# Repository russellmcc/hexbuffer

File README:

This is a simple buffered multiple for eurorack modular synth systems.  Three buffered copies of each input are provided, and the second input is normalled to the first to provide six copies when there is only one input.

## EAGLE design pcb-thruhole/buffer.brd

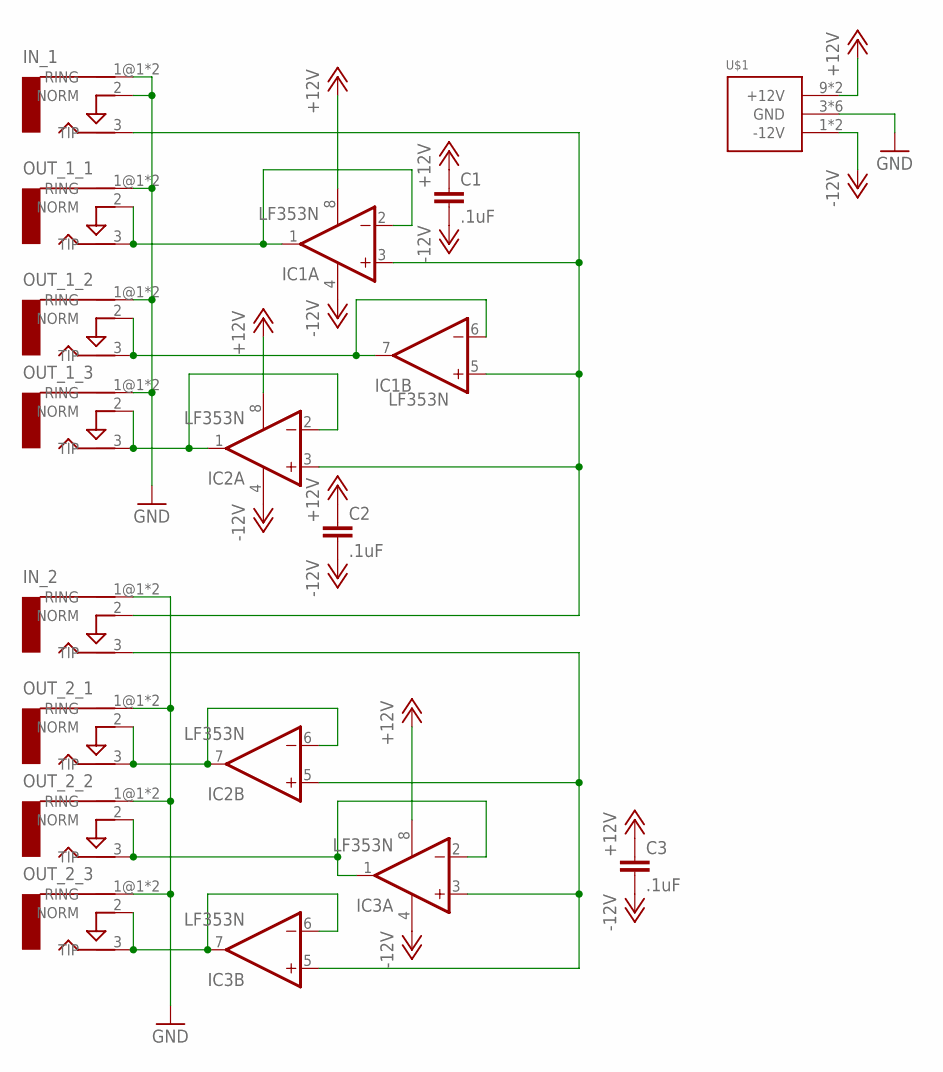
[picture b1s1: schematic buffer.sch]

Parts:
C1, C2, C3: .1uF; CAP-PTH-SMALL
IC1, IC2, IC3: LF353N; DIL08
IN_1, IN_2: AUDIO-JACKERTHENVAR; ERTHENVAR-JACK
OUT_1_1, OUT_1_2, OUT_1_3, OUT_2_1, OUT_2_2, OUT_2_3: AUDIO-JACKERTHENVAR; ERTHENVAR-JACK
U$1: POWER_SIMPLE16; POWER_16

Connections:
+12V: C1.1, C2.1, C3.1, IC1.8 (V+), IC2.8 (V+), IC3.8 (V+), U$1.9 (+12V), U$1.10 (+12V)
-12V: C1.2, C2.2, C3.2, IC1.4 (V-), IC2.4 (V-), IC3.4 (V-), U$1.1 (-12V), U$1.2 (-12V)
GND: IN_1.1@1 (RING), IN_1.1@2 (RING), IN_1.2 (NORM), IN_2.1@1 (RING), IN_2.1@2 (RING), OUT_1_1.1@1 (RING), OUT_1_1.1@2 (RING), OUT_1_2.1@1 (RING), OUT_1_2.1@2 (RING), OUT_1_3.1@1 (RING), OUT_1_3.1@2 (RING), OUT_2_1.1@1 (RING), OUT_2_1.1@2 (RING), OUT_2_2.1@1 (RING), OUT_2_2.1@2 (RING), OUT_2_3.1@1 (RING), OUT_2_3.1@2 (RING), U$1.3 (GND), U$1.4 (GND), U$1.5 (GND), U$1.6 (GND), U$1.7 (GND), U$1.8 (GND)
unnamed: IC1.1 (OUT), IC1.2 (-IN), OUT_1_1.2 (NORM), OUT_1_1.3 (TIP)
unnamed: IC2.1 (OUT), IC2.2 (-IN), OUT_1_3.2 (NORM), OUT_1_3.3 (TIP)
unnamed: IC1.6 (-IN), IC1.7 (OUT), OUT_1_2.2 (NORM), OUT_1_2.3 (TIP)
unnamed: IC1.3 (+IN), IC1.5 (+IN), IC2.3 (+IN), IN_1.3 (TIP), IN_2.2 (NORM)
unnamed: IC2.6 (-IN), IC2.7 (OUT), OUT_2_1.2 (NORM), OUT_2_1.3 (TIP)
unnamed: IC3.6 (-IN), IC3.7 (OUT), OUT_2_3.2 (NORM), OUT_2_3.3 (TIP)
unnamed: IC2.5 (+IN), IC3.3 (+IN), IC3.5 (+IN), IN_2.3 (TIP)
unnamed: IC3.1 (OUT), IC3.2 (-IN), OUT_2_2.2 (NORM), OUT_2_2.3 (TIP)

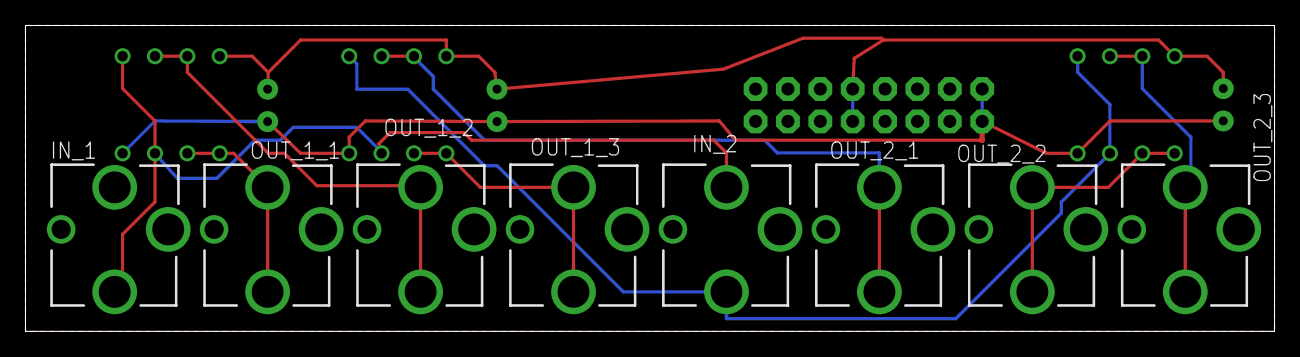
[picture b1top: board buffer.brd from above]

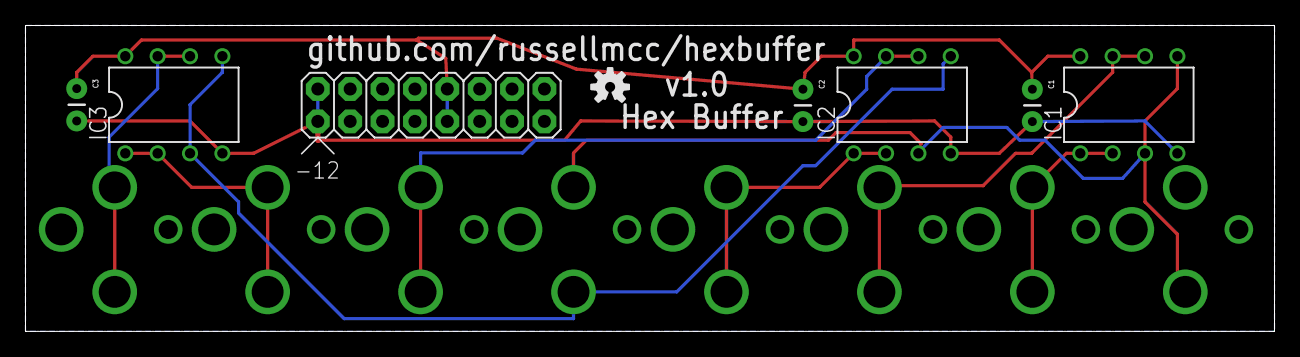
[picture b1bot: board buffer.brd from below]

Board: 2 copper layers, 98.0 x 24.0 mm, 16 parts (8 on the bottom side), 11 nets.

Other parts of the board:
U$6: OSHW-LOGO-S

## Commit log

2012-12-24 initial.
2012-12-24 removed two airwires I accidentally left in.
2012-12-24 fix for bad routing
2012-12-24 made the ground plane the same side as the board and used the DRC to find the correct size
2012-12-24 switched to 10mil isolation on ground planes
2012-12-24 added front panel without art
2012-12-24 added thru hole version
2012-12-24 fix for oopsy
2012-12-24 moved ICs to the back so they don't hit the jacks.
2012-12-26 moved the name to the place layer so it'll show up
2012-12-26 straightened som traces.
2012-12-26 switched panel to 5hp because the board has to be bigger
2012-12-26 added lineart to front panel
2012-12-26 added oshw logo
2012-12-26 added cc license
2012-12-26 added markdown extension
2012-12-26 typo
2012-12-27 added BOM
2012-12-27 added mouser cart
2012-12-27 notes
2013-01-06 added scale for front panel
2013-01-11 added .gitignore
2013-01-24 moved some text off of holes, added url, made version 1.0
2013-01-27 better hole placement
2013-01-27 oops

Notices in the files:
parts and their libraries:
SparkFun: Licensing: CC v3.0 Share-Alike You are welcome to use this library for commercial purposes.
